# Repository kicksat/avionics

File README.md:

avionics
========

# This repo is no longer being updated. Please see the individual repos for the mainboard, solar panels, and antenna.

# License

[Creative Commons Attribution-ShareAlike 4.0 International](https://creativecommons.org/licenses/by-sa/4.0/)

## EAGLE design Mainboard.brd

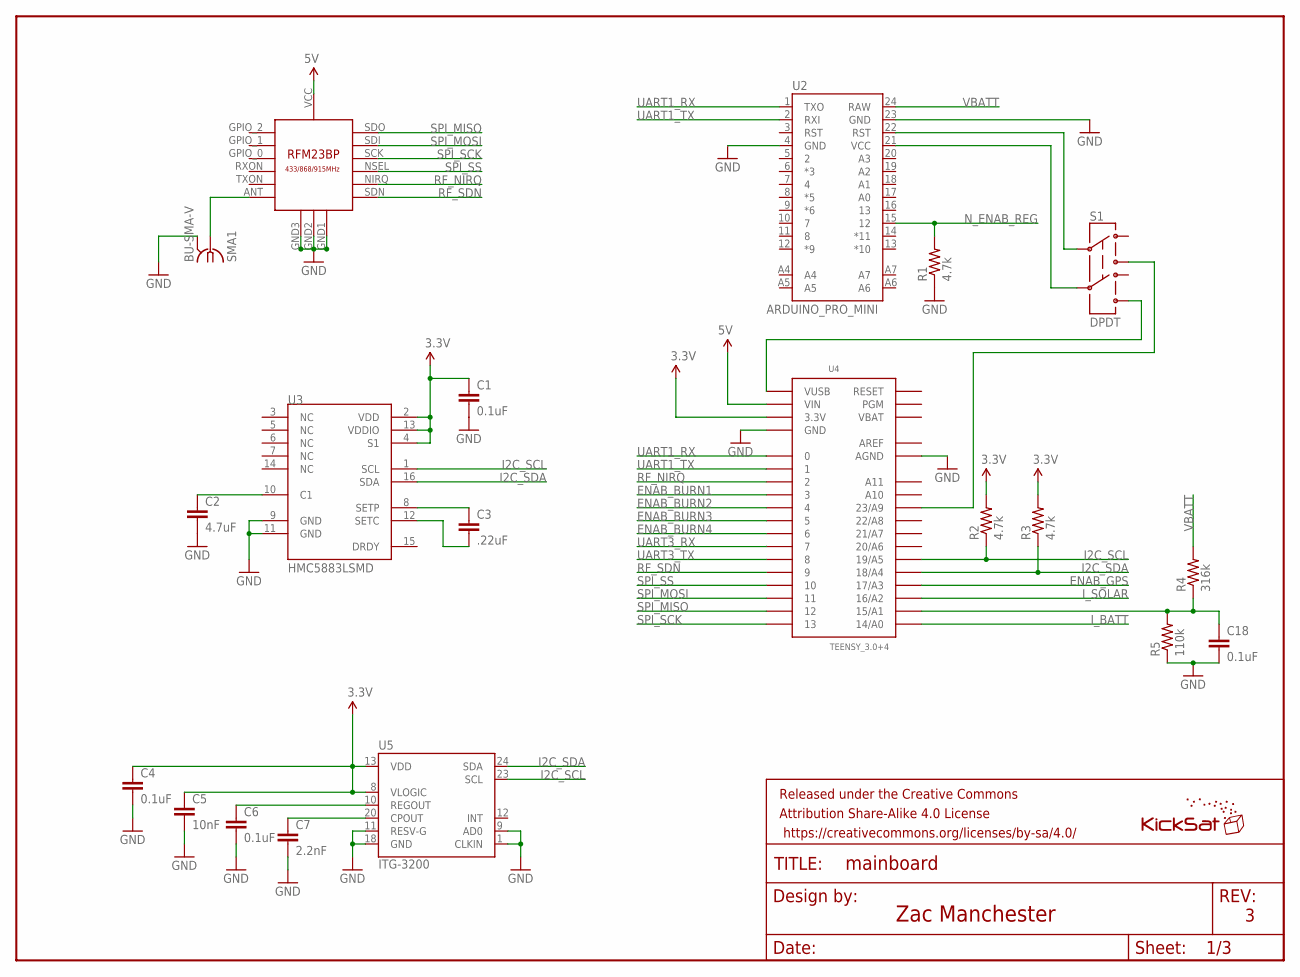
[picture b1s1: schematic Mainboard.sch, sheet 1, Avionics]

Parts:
C1, C4, C6, C18: 0.1uF; 0805
C2: 4.7uF; 0805
C3: .22uF; 0805
C5: 10nF; 0805
C7: 2.2nF; 0805
FRAME1: FRAME-LETTER; CREATIVE_COMMONS
R1, R2, R3: 4.7k; 0805
R4: 316k; 0805
R5: 110k; 0805
S1: DPDT; AYZ0202
SMA1: BU-SMA-V
U1: RFM23BP
U2: ARDUINO_PRO_MINI
U3: HMC5883LSMD; 16LPCC
U4: TEENSY_3.0+4
U5: ITG-3200; QFN-24
U$3: KICKSAT_LOGO

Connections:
3.3V: C1.1, C4.1, C5.1, R2.2, R3.2, U3.2 (VDD), U3.4 (S1), U3.13 (VDDIO), U4.3.3V, U4.3.3V1 (3.3V), U5.8 (VLOGIC), U5.13 (VDD); also elsewhere on the board
5V: U1.VCC, U4.VIN; also elsewhere on the board
AREF: U4.AREF
ENAB_BURN1: U4.3; also elsewhere on the board
ENAB_BURN2: U4.4; also elsewhere on the board
ENAB_BURN3: U4.5; also elsewhere on the board
ENAB_BURN4: U4.6; also elsewhere on the board
ENAB_GPS: U4.17/A3; also elsewhere on the board
GND: C1.2, C2.2, C4.2, C5.2, C6.2, C7.2, C18.2, R1.1, R5.1, SMA1.2, SMA1.3 (2), SMA1.4 (2), SMA1.5 (2), U1.GND1, U1.GND2, U1.GND3, U2.4 (GND), U2.23 (GND), U3.9 (GND), U3.11 (GND), U4.AGND, U4.GND, U4.GND1 (GND), U5.1 (CLKIN), U5.9 (AD0), U5.11 (RESV-G), U5.18 (GND); also elsewhere on the board
I2C_SCL: R2.1, U3.1 (SCL), U4.19/A5, U5.23 (SCL)
I2C_SDA: R3.1, U3.16 (SDA), U4.18/A4, U5.24 (SDA)
I_BATT: U4.14/A0; also elsewhere on the board
I_SOLAR: U4.16/A2; also elsewhere on the board
unnamed: S1.3, U4.23/A9
unnamed: S1.6, U4.VUSB
unnamed: SMA1.1, U1.ANT
unnamed: C18.1, R4.1, R5.2, U4.15/A1
unnamed: C7.1, U5.20 (CPOUT)
unnamed: C6.1, U5.10 (REGOUT)
unnamed: C2.1, U3.10 (C1)
unnamed: C3.1, U3.8 (SETP)
unnamed: C3.2, U3.12 (SETC)
N_ENAB_REG: R1.2, U2.15 (12); also elsewhere on the board
PGM_RST: S1.2, U2.22 (RST)
PGM_VCC: S1.5, U2.21 (VCC)
RF_NIRQ: U1.NIRQ, U4.2
RF_SDN: U1.SDN, U4.9
SPI_MISO: U1.SDO, U4.12
SPI_MOSI: U1.SDI, U4.11
SPI_SCK: U1.SCK, U4.13
SPI_SS: U1.NSEL, U4.10
UART1_RX: U2.1 (TXO), U4.0
UART1_TX: U2.2 (RXI), U4.1
UART3_RX: U4.7; also elsewhere on the board
UART3_TX: U4.8; also elsewhere on the board
VBAT: U4.VBAT
VBATT: R4.2, U2.24 (RAW); also elsewhere on the board

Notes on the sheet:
Zac Manchester

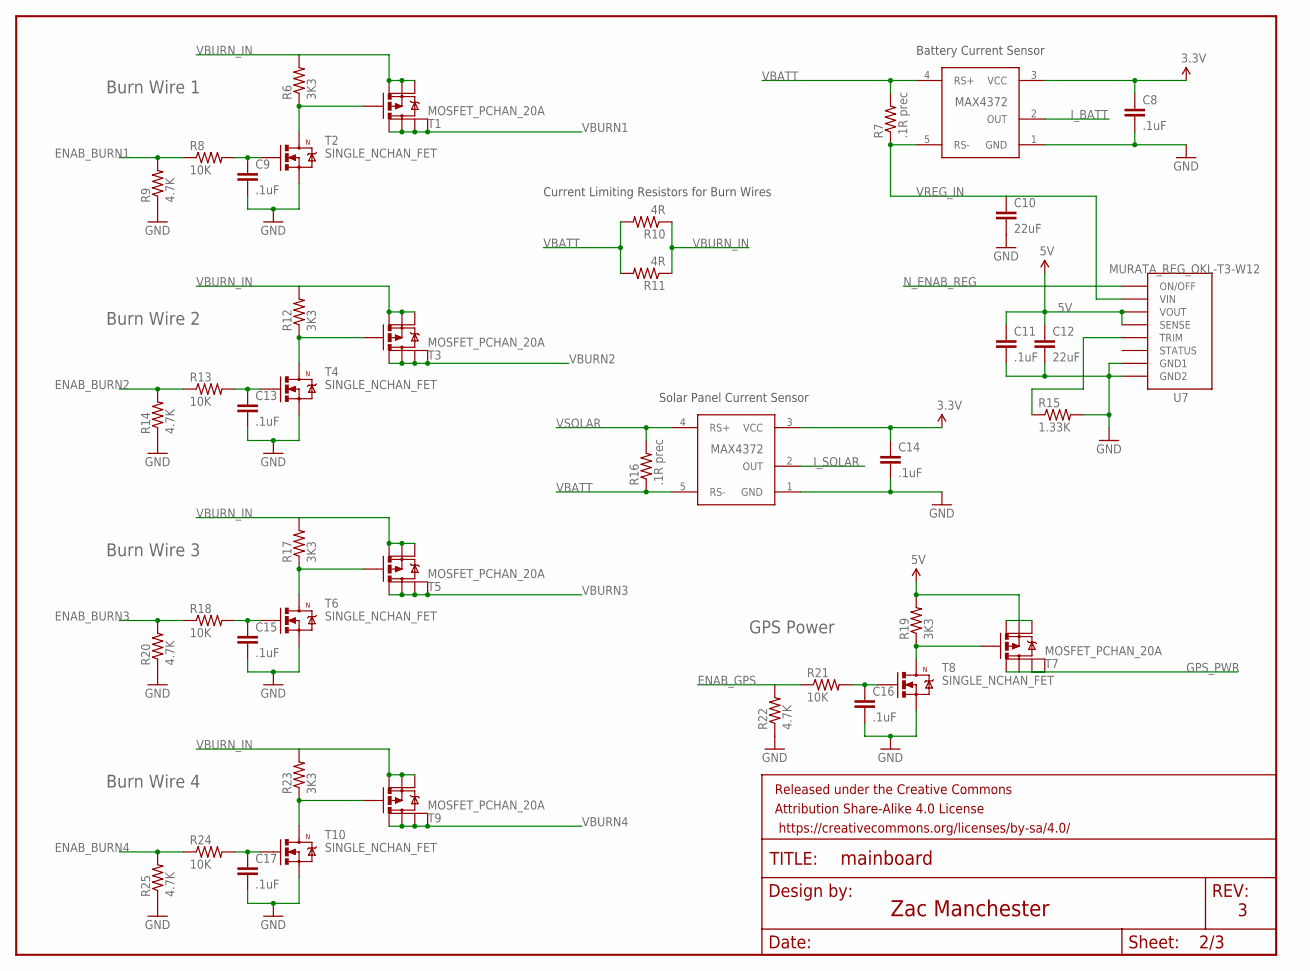
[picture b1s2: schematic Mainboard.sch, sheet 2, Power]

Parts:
C8, C9, C11, C13, C14, C15, C16, C17: .1uF; 0805
C10, C12: 22uF; 1206
FRAME2: FRAME-LETTER; CREATIVE_COMMONS
R6, R12, R17, R19, R23: 3K3; 0805
R7, R16: .1R prec; 0805
R8, R13, R18, R21, R24: 10K; 0805
R9, R14, R20, R22, R25: 4.7K; 0805
R10, R11: 4R; R2512
R15: 1.33K; 0805
T1, T3, T5, T7, T9: MOSFET_PCHAN_20A; SO8
T2, T4, T6, T8, T10: SINGLE_NCHAN_FET; SOT23-3
U6, U8: CURRENT_MAX4372; SOT23-5
U7: MURATA_REG_OKL-T3-W12; MURATA_REG_OKL-T6-W12

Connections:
3.3V: C8.1, C14.1, U6.3 (VCC), U8.3 (VCC); also elsewhere on the board
5V: C11.1, C12.1, R19.2, T7.1 (S), T7.2 (S), T7.3 (S), U7.4 (VOUT), U7.5 (SENSE); also elsewhere on the board
ENAB_BURN1: R8.1, R9.2; also elsewhere on the board
ENAB_BURN2: R13.1, R14.2; also elsewhere on the board
ENAB_BURN3: R18.1, R20.2; also elsewhere on the board
ENAB_BURN4: R24.1, R25.2; also elsewhere on the board
ENAB_GPS: R21.1, R22.2; also elsewhere on the board
GND: C8.2, C9.2, C10.2, C11.2, C12.2, C13.2, C14.2, C15.2, C16.2, C17.2, R9.1, R14.1, R15.2, R20.1, R22.1, R25.1, T2.2 (S), T4.2 (S), T6.2 (S), T8.2 (S), T10.2 (S), U6.1 (GND), U7.3 (GND1), U7.7 (GND2), U8.1 (GND); also elsewhere on the board
GPS_PWR: T7.5 (D), T7.6 (D), T7.7 (D), T7.8 (D); also elsewhere on the board
I_BATT: U6.2 (OUT); also elsewhere on the board
I_SOLAR: U8.2 (OUT); also elsewhere on the board
unnamed: C13.1, R13.2, T4.1 (G)
unnamed: R12.1, T3.4 (G), T4.3 (D)
unnamed: C15.1, R18.2, T6.1 (G)
unnamed: R17.1, T5.4 (G), T6.3 (D)
unnamed: R15.1, U7.6 (TRIM)
unnamed: C17.1, R24.2, T10.1 (G)
unnamed: R23.1, T9.4 (G), T10.3 (D)
unnamed: C16.1, R21.2, T8.1 (G)
unnamed: R19.1, T7.4 (G), T8.3 (D)
unnamed: C9.1, R8.2, T2.1 (G)
unnamed: R6.1, T1.4 (G), T2.3 (D)
N_ENAB_REG: U7.1 (ON/OFF); also elsewhere on the board
VBATT: R7.2, R10.2, R11.2, R16.1, U6.4 (RS+), U8.5 (RS-); also elsewhere on the board
VBURN1: T1.5 (D), T1.6 (D), T1.7 (D), T1.8 (D); also elsewhere on the board
VBURN2: T3.5 (D), T3.6 (D), T3.7 (D), T3.8 (D); also elsewhere on the board
VBURN3: T5.5 (D), T5.6 (D), T5.7 (D), T5.8 (D); also elsewhere on the board
VBURN4: T9.5 (D), T9.6 (D), T9.7 (D), T9.8 (D); also elsewhere on the board
VBURN_IN: R6.2, R10.1, R11.1, R12.2, R17.2, R23.2, T1.1 (S), T1.2 (S), T1.3 (S), T3.1 (S), T3.2 (S), T3.3 (S), T5.1 (S), T5.2 (S), T5.3 (S), T9.1 (S), T9.2 (S), T9.3 (S)
VREG_IN: C10.1, R7.1, U6.5 (RS-), U7.2 (VIN)
VSOLAR: R16.2, U8.4 (RS+); also elsewhere on the board

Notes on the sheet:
Burn Wire 1
Burn Wire 2
Burn Wire 3
Solar Panel Current Sensor
Battery Current Sensor
Burn Wire 4
Current Limiting Resistors for Burn Wires
Zac Manchester
GPS Power

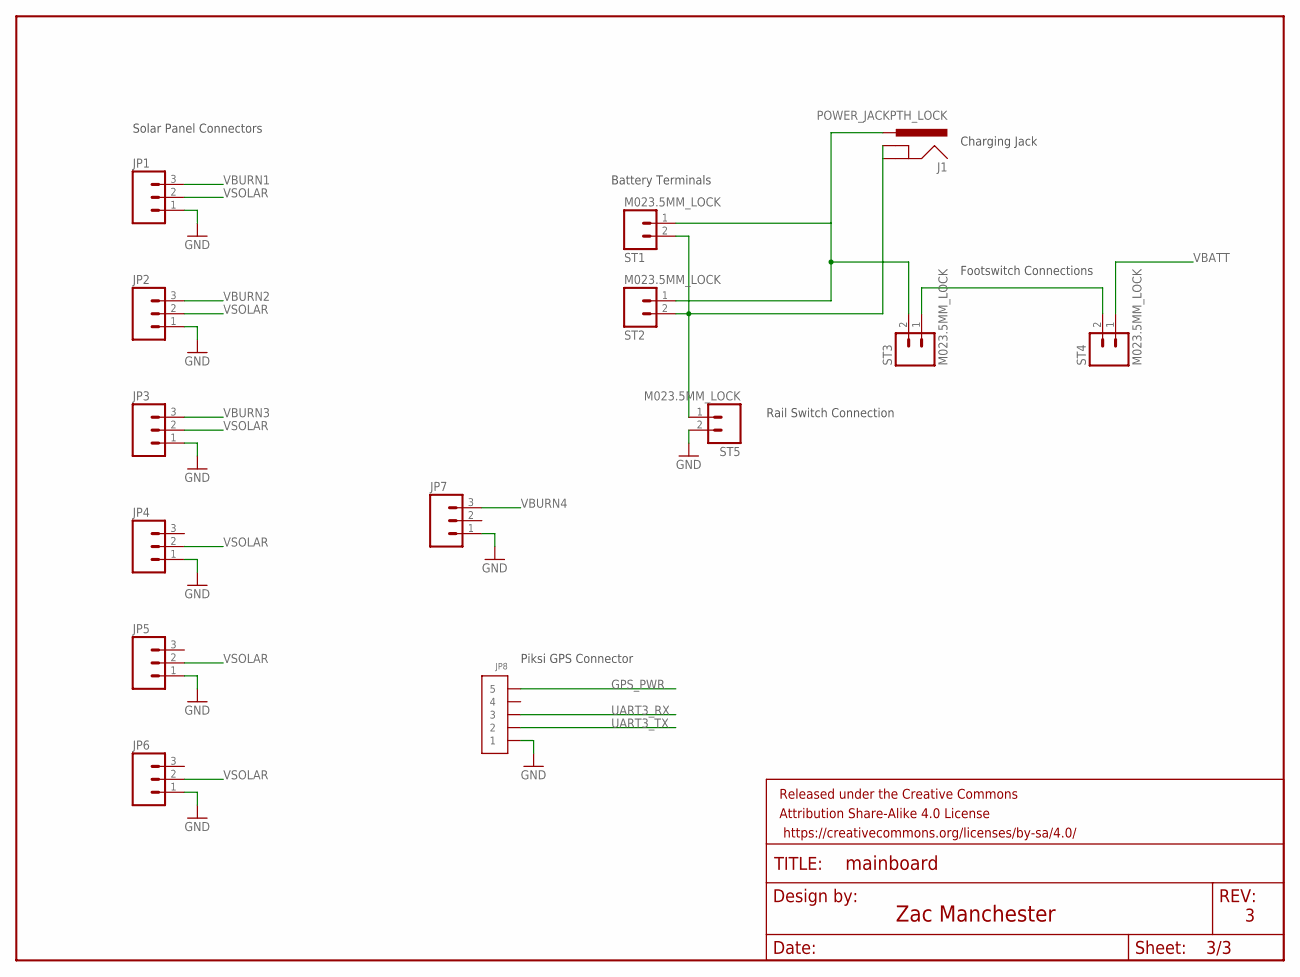
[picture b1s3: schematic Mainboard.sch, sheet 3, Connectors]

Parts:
FRAME3: FRAME-LETTER; CREATIVE_COMMONS
J1: POWER_JACKPTH_LOCK; POWER_JACK_PTH_LOCK
JP1, JP2, JP3, JP4, JP5, JP6, JP7: M03POLAR_LOCK; MOLEX-1X3_LOCK
JP8: CONN_5-1-53261; PB-53261-05
ST1, ST2, ST3, ST4, ST5: M023.5MM_LOCK; SCREWTERMINAL-3.5MM-2_LOCK

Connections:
BATT_INPUT: J1.PWR, ST1.1, ST2.1, ST3.2
GND: JP1.1, JP2.1, JP3.1, JP4.1, JP5.1, JP6.1, JP7.1, JP8.1, ST5.2; also elsewhere on the board
GPS_PWR: JP8.5; also elsewhere on the board
unnamed: J1.GND, J1.GNDBREAK, ST1.2, ST2.2, ST5.1
unnamed: ST3.1, ST4.2
UART3_RX: JP8.3; also elsewhere on the board
UART3_TX: JP8.2; also elsewhere on the board
VBATT: ST4.1; also elsewhere on the board
VBURN1: JP1.3; also elsewhere on the board
VBURN2: JP2.3; also elsewhere on the board
VBURN3: JP3.3; also elsewhere on the board
VBURN4: JP7.3; also elsewhere on the board
VSOLAR: JP1.2, JP2.2, JP3.2, JP4.2, JP5.2, JP6.2; also elsewhere on the board

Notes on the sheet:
Footswitch Connections
Solar Panel Connectors
Battery Terminals
Rail Switch Connection
Charging Jack
Piksi GPS Connector
Zac Manchester

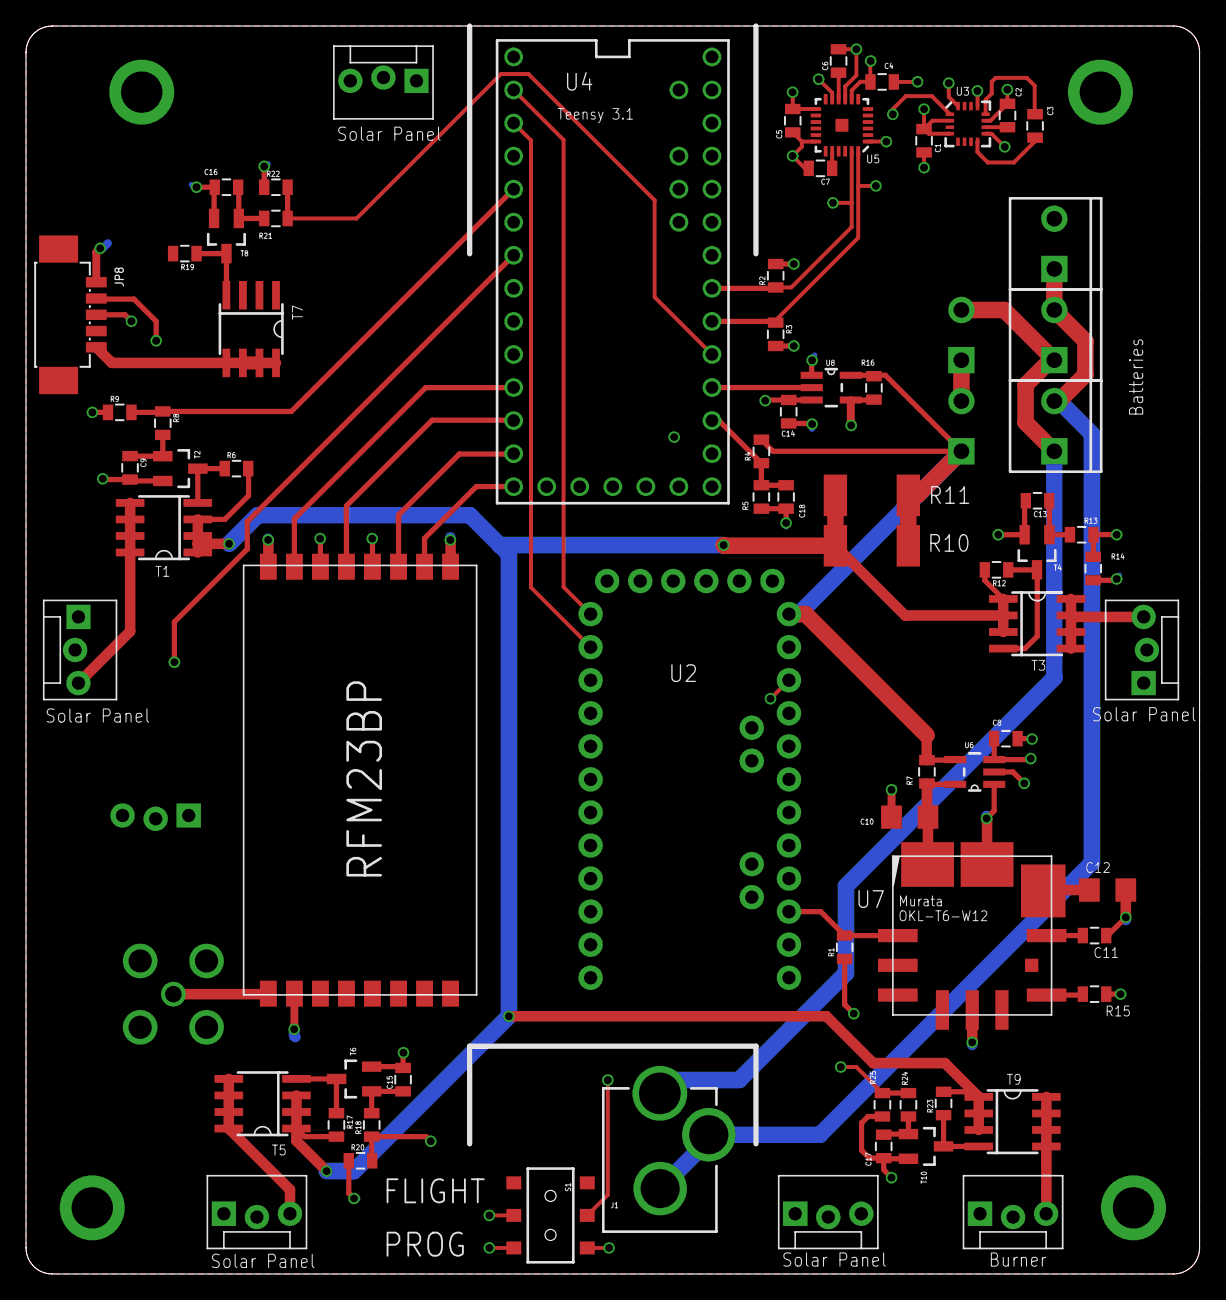
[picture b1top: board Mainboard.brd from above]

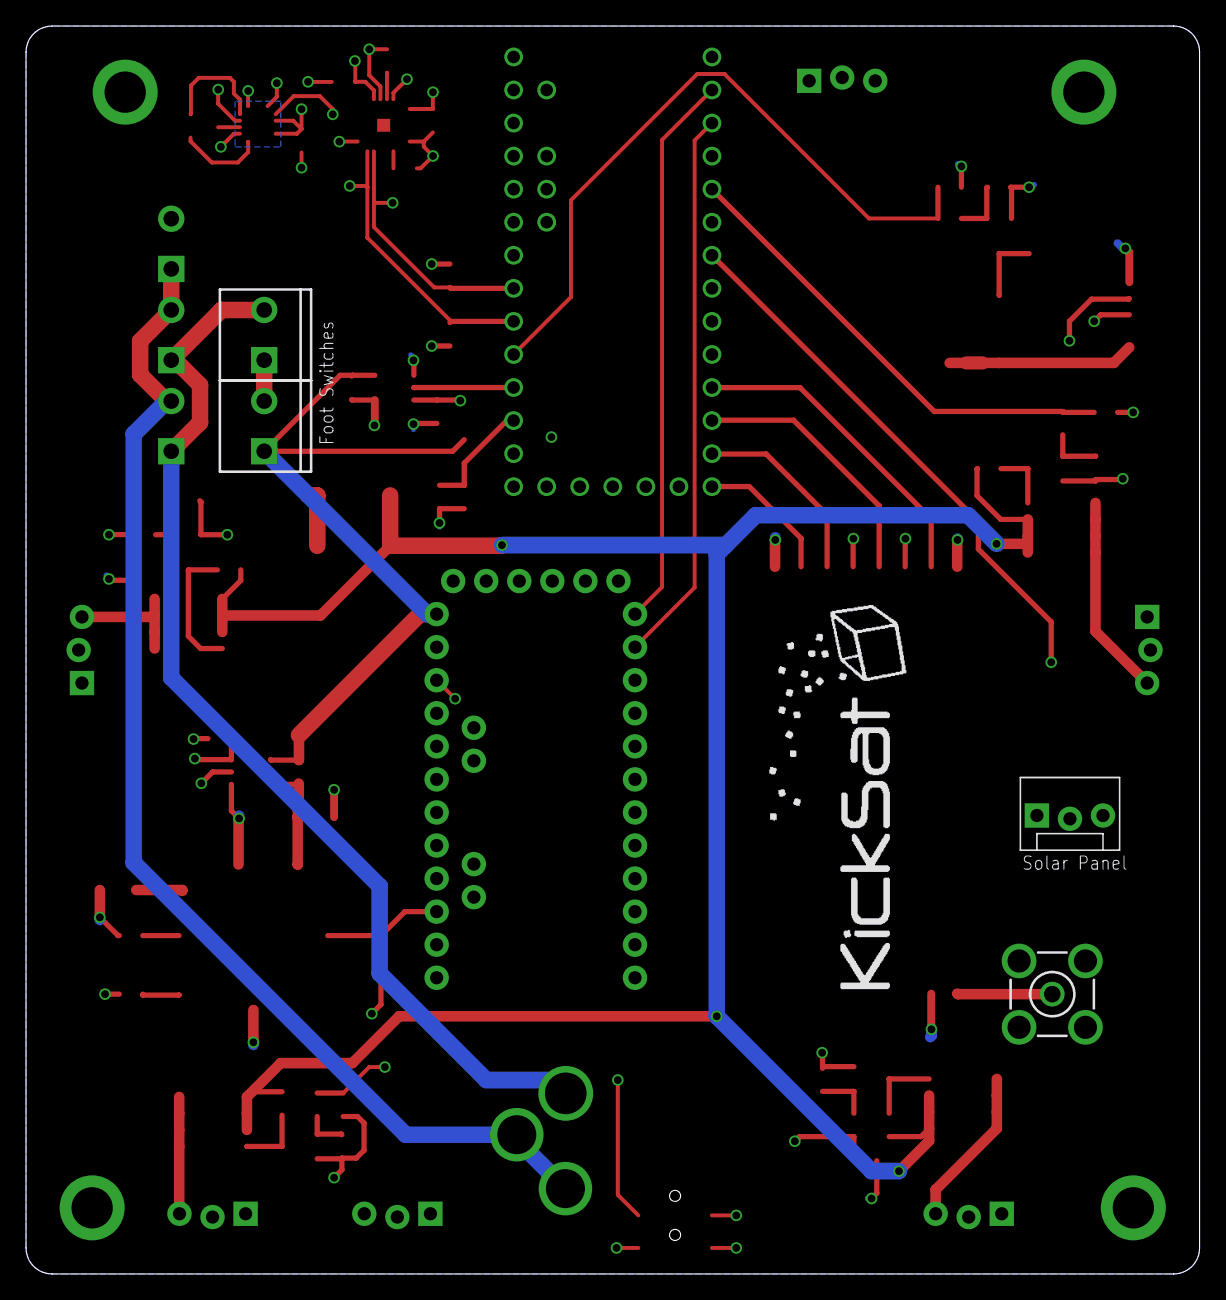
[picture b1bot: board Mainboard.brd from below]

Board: 4 copper layers, 90.2 x 95.9 mm, 81 parts (5 on the bottom side), 57 nets.

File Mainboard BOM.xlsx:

Qty | Value | Device | Package | Parts | Description
3 | 4.7k | Resistor | 0805 | R1, R2, R3 | Resistor
1 | 120k | Resistor | 0805 | R4 | Resistor
1 | 68k | Resistor | 0805 | R5 | Resistor
5 | 3K3 | Resistor | 0805 | R6, R12, R17, R19, R23 | Resistor
2 | .1R prec | Resistor | 0805 | R7, R16 | Resistor
5 | 10K | Resistor | 0805 | R8, R13, R18, R21, R24 | Resistor
5 | 4.7K | Resistor | 0805 | R9, R14, R20, R22, R25 | Resistor
2 | 4R | Resistor | 2512 | R10, R11 | Resistor
1 | 1.33K | Resistor | 0805 | R15 | Resistor
3 | 0.1uF | Capacitor | 0805 | C1, C4, C6 | Capacitor
1 | 4.7uF | Capacitor | 0805 | C2 | Capacitor
1 | .22uF | Capacitor | 0805 | C3 | Capacitor
1 | 10nF | Capacitor | 0805 | C5 | Capacitor
1 | 2.2nF | Capacitor | 0805 | C7 | Capacitor
8 | .1uF | Capacitor | 0805 | C8, C9, C11, C13, C14, C15, C16, C17 | Capacitor
2 | 22uF | Capacitor | 1206 | C10, C12 | Capacitor
5 | MOSFET_PCHAN_20A | MOSFET_PCHAN_20A | SO8 | T1, T3, T5, T7, T9 | Power MOSFET for Burn Wires
5 | SINGLE_NCHAN_FET | SINGLE_NCHAN_FET | SOT23-3 | T2, T4, T6, T8, T10 | MOSFET for burn wire circuit
1 | RFM23BP | RFM23BP | RFM23BP | U1 | HopeRF RFM23BP Radio
1 | ARDUINO_PRO_MINI | ARDUINO_PRO_MINI | ARDUINO_PRO_MINI | U2 | Watchdog MCU
1 | HMC5883LSMD | HMC5883LSMD | 16LPCC | U3 | 3 Axis Digital Compass IC
1 | TEENSY_3.0+4 | TEENSY_3.0+4 | TEENSY_3.0+4 | U4 | Flight computer MCU
1 | ITG-3200 | ITG-3200 | QFN-24 | U5 | ITG-3200 3-axis gyro, digital output, qfn24 package
2 | CURRENT_MAX4372 | CURRENT_MAX4372 | SOT23-5 | U6, U8 | Current Sense Amplifier
1 | MURATA_REG_OKL-T3-W12 | MURATA_REG_OKL-T6-W12 | MURATA_REG_OKL-T6-W12 | U7 | Switching Regulator
5 | M023.5MM_LOCK | M023.5MM_LOCK | SCREWTERMINAL-3.5MM-2_LOCK | ST1, ST2, ST3, ST4, ST5 | Screw terminals for battery + foot switch connections
1 | BU-SMA-V | BU-SMA-V | BU-SMA-V | SMA1 | Antenna connector (MCX)
1 | CONN_5-1-53261 | CONN_5-1-53261 | PB-53261-05 | JP8 | Piksi GPS connector
7 | M03POLAR_LOCK | M03POLAR_LOCK | MOLEX-1X3_LOCK | JP1, JP2, JP3, JP4, JP5, JP6, JP7 | Solar Panel Connectors
1 | POWER_JACKPTH_LOCK | POWER_JACKPTH_LOCK | POWER_JACK_PTH_LOCK | J1 | Charging Jack
1 | DPDT | SWITCH-DPDTAYZ0202 | AYZ0202 | S1 | Switch for MCU programming mode

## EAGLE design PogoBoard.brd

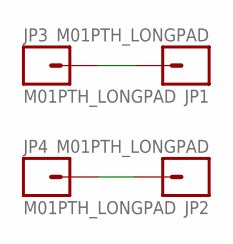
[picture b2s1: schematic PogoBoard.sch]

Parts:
JP1, JP2, JP3, JP4: M01PTH_LONGPAD; 1X01_LONGPAD

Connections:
GND: JP1.1, JP3.1
VSOLAR: JP2.1, JP4.1

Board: 2 copper layers, 4 parts (0 on the bottom side), 2 nets, no tracks yet.

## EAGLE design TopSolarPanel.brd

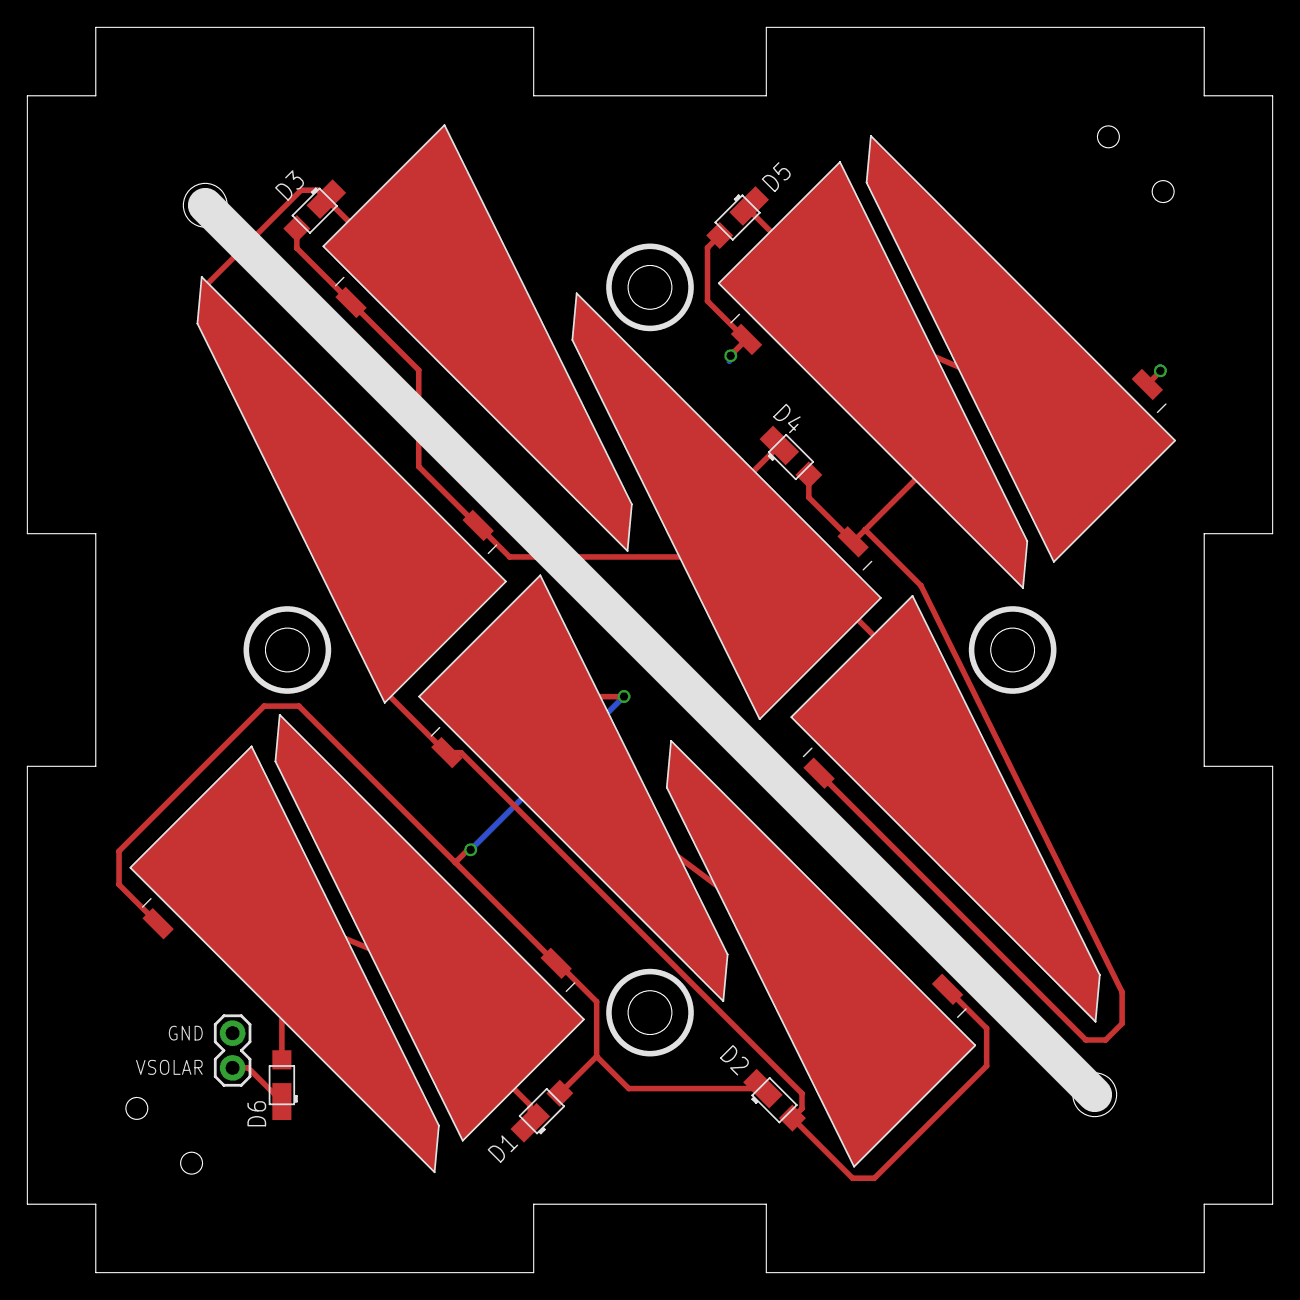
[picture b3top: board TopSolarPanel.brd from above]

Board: 2 copper layers, 91.0 x 91.0 mm, 19 parts (1 on the bottom side), 7 nets.

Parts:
D1, D2, D3, D4, D5, D6: SB_DIODE
FRAME1: FRAME-LETTER; CREATIVE_COMMONS
JP5: M02PTH; 1X02
SL1, SL2, SL3, SL4, SL5, SL6, SL7, SL8, SL9, SL10: SOLAR_CELL
U$1: KICKSAT_LOGO

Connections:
GND: D5.POS, JP5.1, SL9.1, SL10.1
unnamed: D1.NEG, D6.POS, SL1.2, SL2.2
unnamed: D2.POS, D3.NEG, SL3.1, SL4.1, SL5.2, SL6.2
unnamed: D3.POS, D4.NEG, SL5.1, SL6.1, SL7.2, SL8.2
unnamed: D1.POS, D2.NEG, SL1.1, SL2.1, SL3.2, SL4.2
unnamed: D4.POS, D5.NEG, SL7.1, SL8.1, SL9.2, SL10.2
VSOLAR: D6.NEG, JP5.2

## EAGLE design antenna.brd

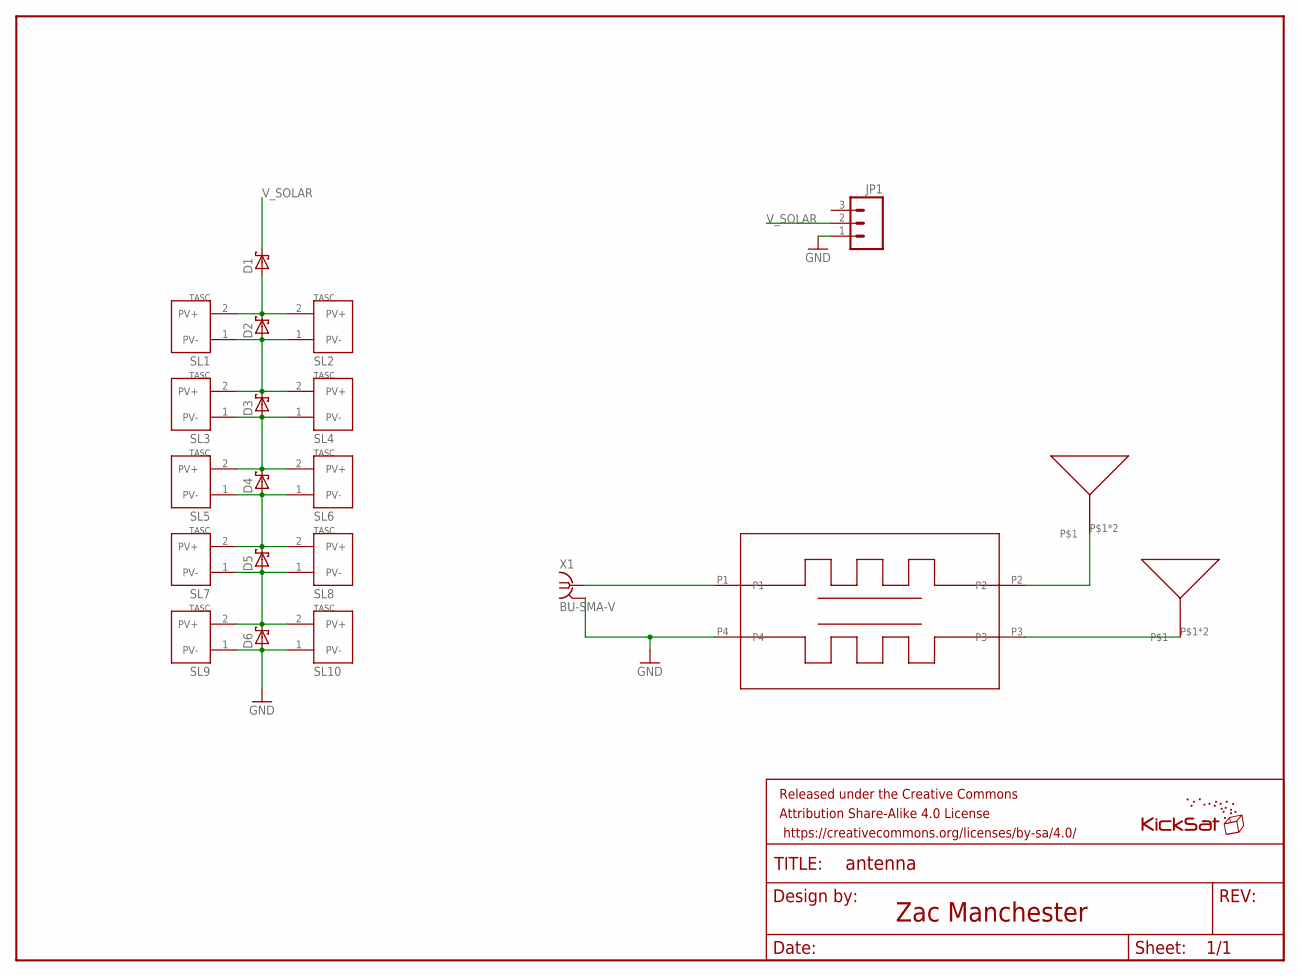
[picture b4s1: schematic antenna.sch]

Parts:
B1: BALUN
D1, D2, D3, D4, D5, D6: SB_DIODE
FRAME1: FRAME-LETTER; CREATIVE_COMMONS
JP1: M03POLAR_LOCK; MOLEX-1X3_LOCK
SL1, SL2, SL3, SL4, SL5, SL6, SL7, SL8, SL9, SL10: SOLAR_CELL
U$1, U$2: TAPEANTENNA
U$3: KICKSAT_LOGO
X1: BU-SMA-V

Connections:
GND: B1.P4, D6.POS, JP1.1, SL9.1 (PV-), SL10.1 (PV-), X1.2, X1.3 (2), X1.4 (2), X1.5 (2)
unnamed: B1.P1, X1.1
unnamed: D1.POS, D2.NEG, SL1.2 (PV+), SL2.2 (PV+)
unnamed: D3.POS, D4.NEG, SL3.1 (PV-), SL4.1 (PV-), SL5.2 (PV+), SL6.2 (PV+)
unnamed: D4.POS, D5.NEG, SL5.1 (PV-), SL6.1 (PV-), SL7.2 (PV+), SL8.2 (PV+)
unnamed: D2.POS, D3.NEG, SL1.1 (PV-), SL2.1 (PV-), SL3.2 (PV+), SL4.2 (PV+)
unnamed: D5.POS, D6.NEG, SL7.1 (PV-), SL8.1 (PV-), SL9.2 (PV+), SL10.2 (PV+)
RFN: B1.P2, U$1.P$1, U$1.P$2
RFP: B1.P3, U$2.P$1, U$2.P$2
V_SOLAR: D1.NEG, JP1.2

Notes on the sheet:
Zac Manchester

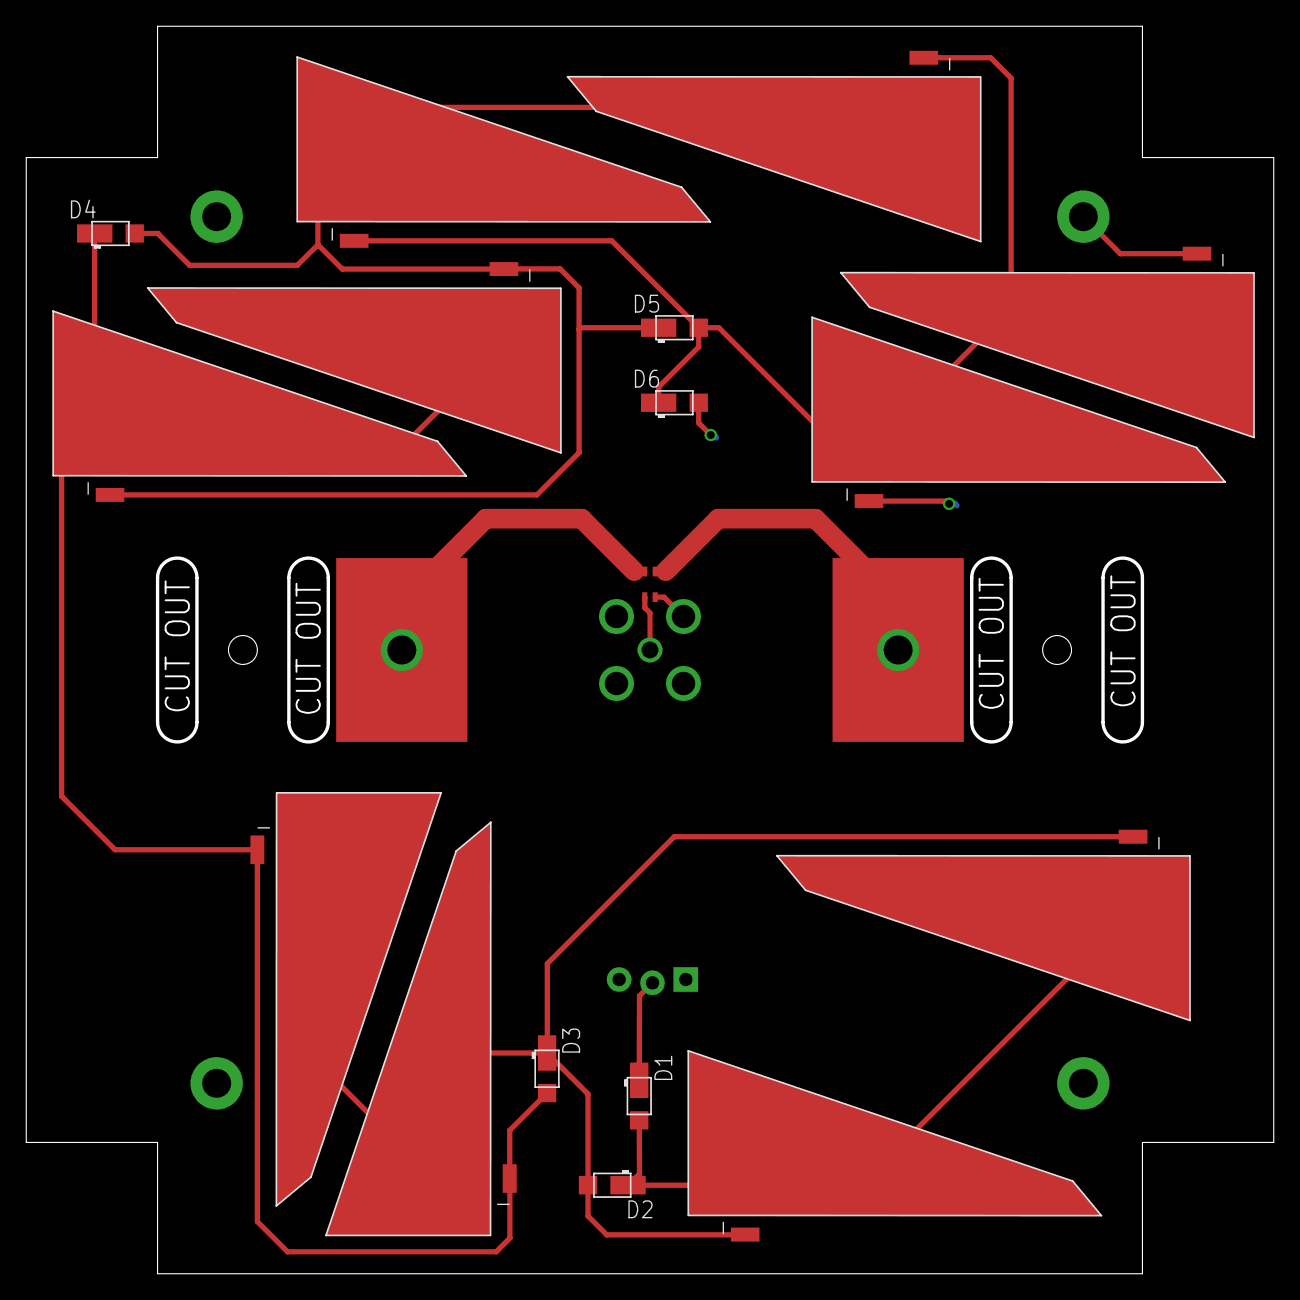
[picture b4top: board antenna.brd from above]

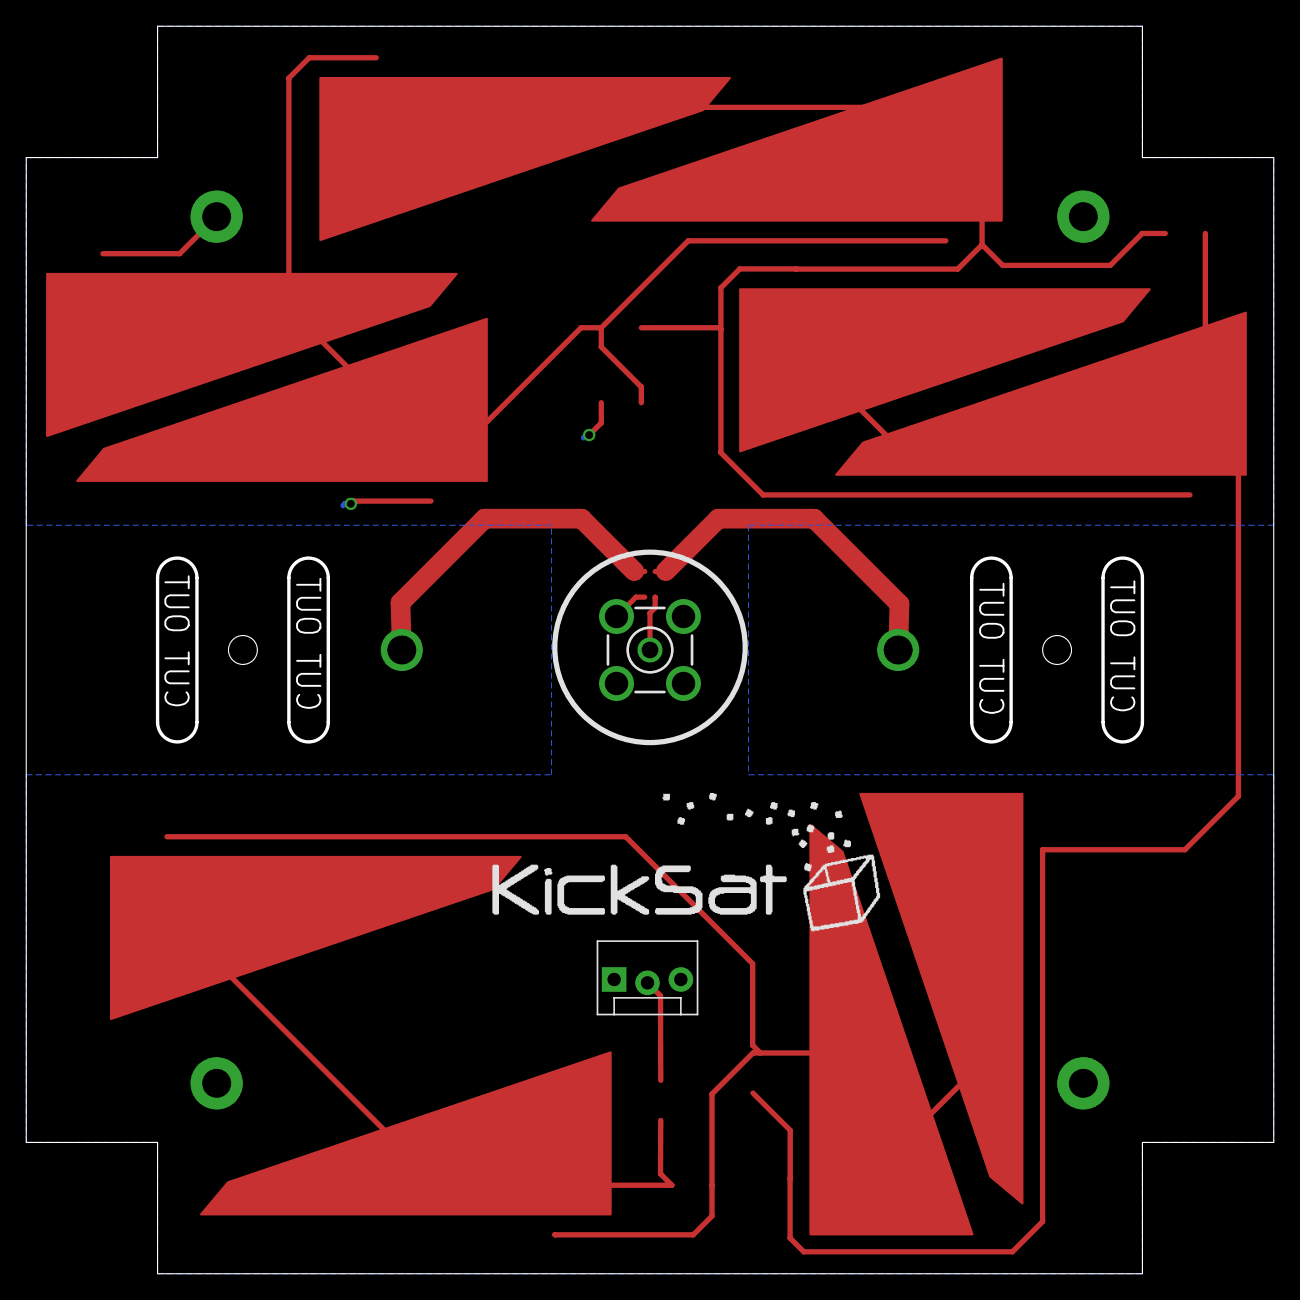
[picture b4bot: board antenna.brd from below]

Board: 2 copper layers, 95.0 x 95.0 mm, 23 parts (3 on the bottom side), 10 nets.

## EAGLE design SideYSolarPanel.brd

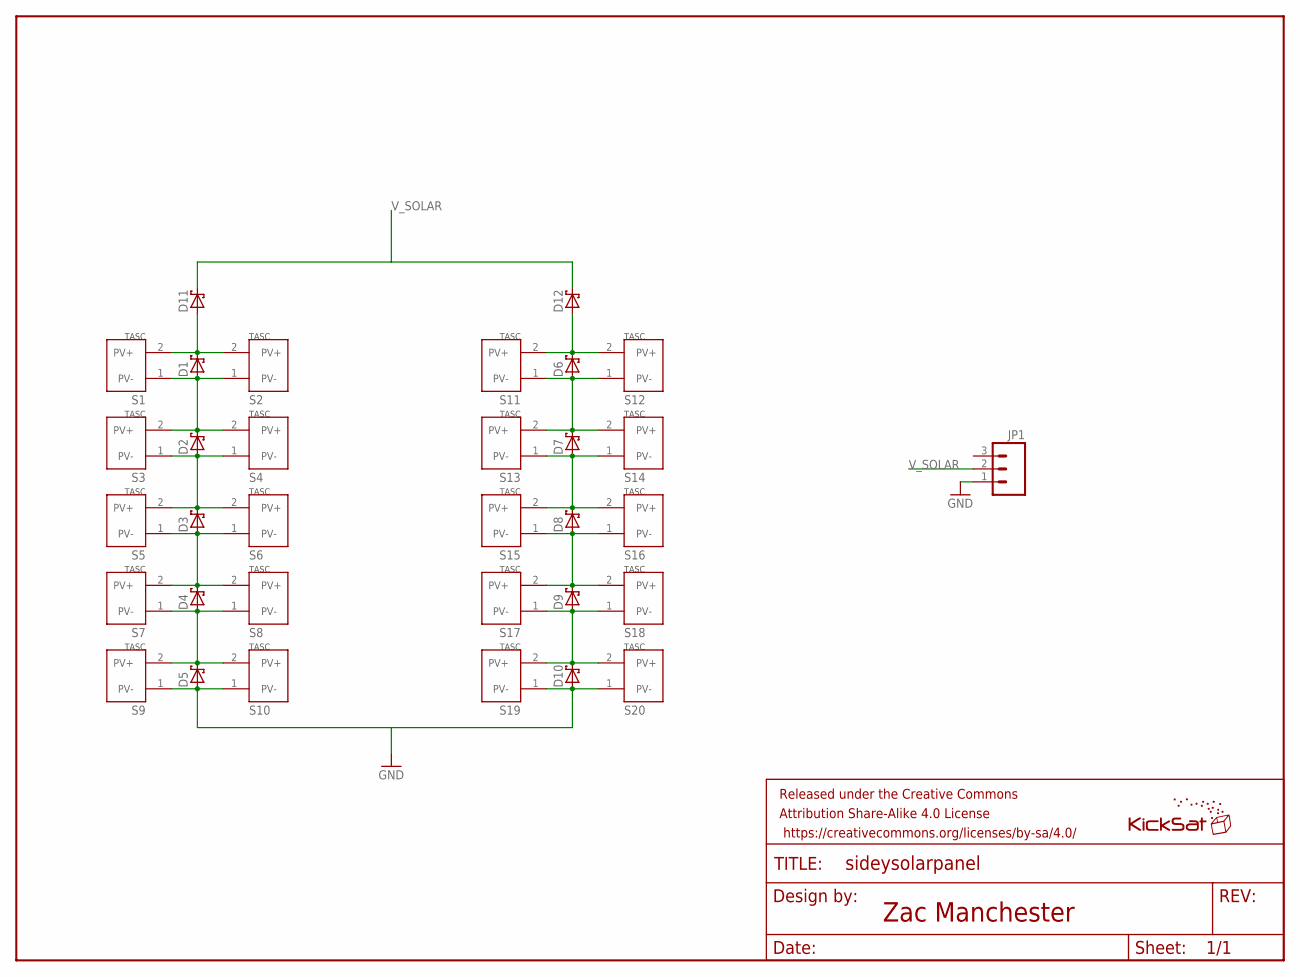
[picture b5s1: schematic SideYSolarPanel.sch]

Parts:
D1, D2, D3, D4, D5, D6, D7, D8, D9, D10, D11, D12: SB_DIODE
FRAME1: FRAME-LETTER; CREATIVE_COMMONS
JP1: M03POLAR_LOCK; MOLEX-1X3_LOCK
S1, S2, S3, S4, S5, S6, S7, S8, S9, S10, S11, S12, S13, S14, S15, S16, S17, S18, S19, S20: SOLAR_CELL
U$1: KICKSAT_LOGO

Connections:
GND: D5.POS, D10.POS, JP1.1, S9.1 (PV-), S10.1 (PV-), S19.1 (PV-), S20.1 (PV-)
unnamed: D6.POS, D7.NEG, S11.1 (PV-), S12.1 (PV-), S13.2 (PV+), S14.2 (PV+)
unnamed: D6.NEG, D12.POS, S11.2 (PV+), S12.2 (PV+)
unnamed: D7.POS, D8.NEG, S13.1 (PV-), S14.1 (PV-), S15.2 (PV+), S16.2 (PV+)
unnamed: D1.NEG, D11.POS, S1.2 (PV+), S2.2 (PV+)
unnamed: D8.POS, D9.NEG, S15.1 (PV-), S16.1 (PV-), S17.2 (PV+), S18.2 (PV+)
unnamed: D2.POS, D3.NEG, S3.1 (PV-), S4.1 (PV-), S5.2 (PV+), S6.2 (PV+)
unnamed: D3.POS, D4.NEG, S5.1 (PV-), S6.1 (PV-), S7.2 (PV+), S8.2 (PV+)
unnamed: D9.POS, D10.NEG, S17.1 (PV-), S18.1 (PV-), S19.2 (PV+), S20.2 (PV+)
unnamed: D1.POS, D2.NEG, S1.1 (PV-), S2.1 (PV-), S3.2 (PV+), S4.2 (PV+)
unnamed: D4.POS, D5.NEG, S7.1 (PV-), S8.1 (PV-), S9.2 (PV+), S10.2 (PV+)
V_SOLAR: D11.NEG, D12.NEG, JP1.2

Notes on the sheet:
Zac Manchester

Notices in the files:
parts and their libraries:
SparkFun-Connectors: Licensing: Creative Commons ShareAlike 4.0 International - https://creativecommons.org/licenses/by-sa/4.0
SparkFun-Aesthetics: Released under the Creative Commons Attribution Share-Alike 4.0 License
SparkFun-Aesthetics: Released under the Creative Commons
